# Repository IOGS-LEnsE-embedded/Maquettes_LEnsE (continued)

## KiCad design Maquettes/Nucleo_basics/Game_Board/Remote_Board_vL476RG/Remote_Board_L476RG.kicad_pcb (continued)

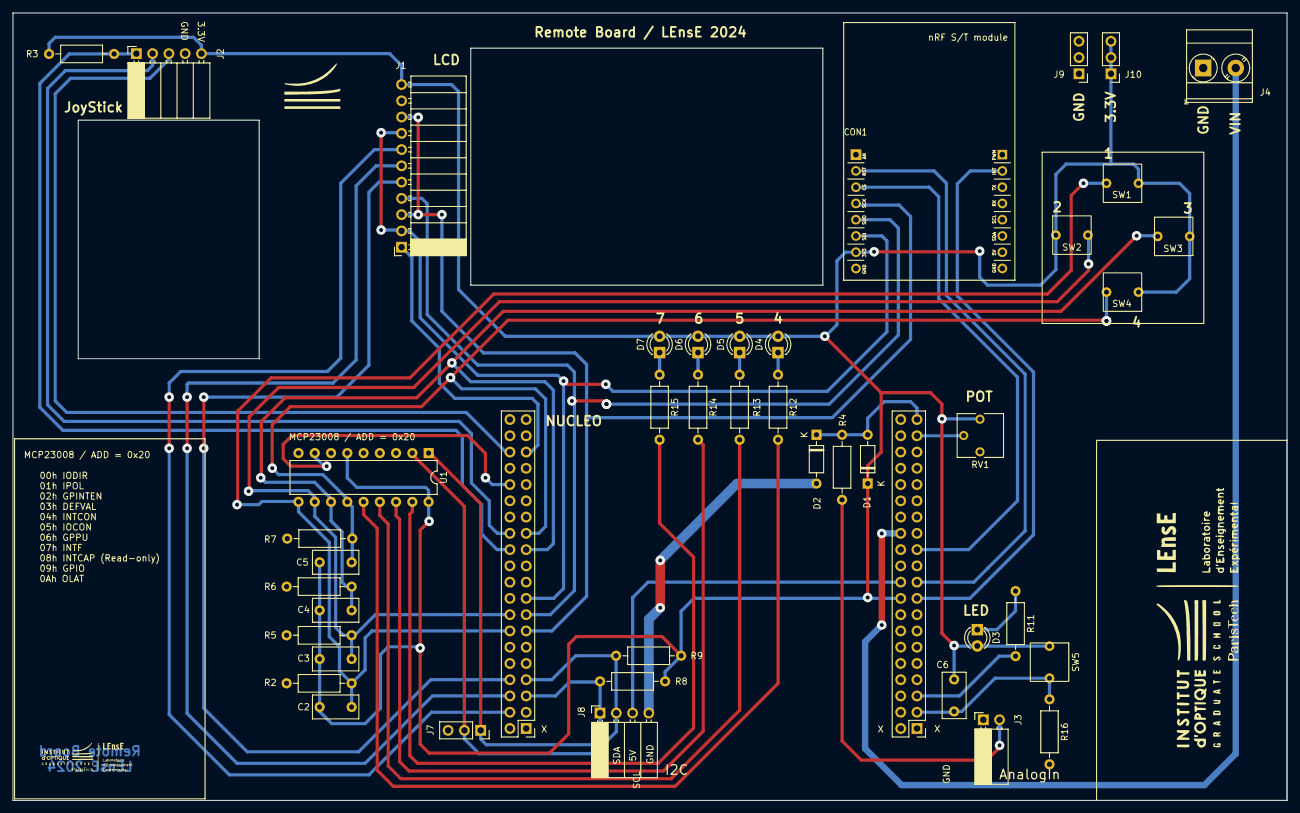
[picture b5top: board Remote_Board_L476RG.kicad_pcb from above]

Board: 2 copper layers, 199.0 x 123.0 mm, 44 parts (0 on the bottom side), 38 nets.

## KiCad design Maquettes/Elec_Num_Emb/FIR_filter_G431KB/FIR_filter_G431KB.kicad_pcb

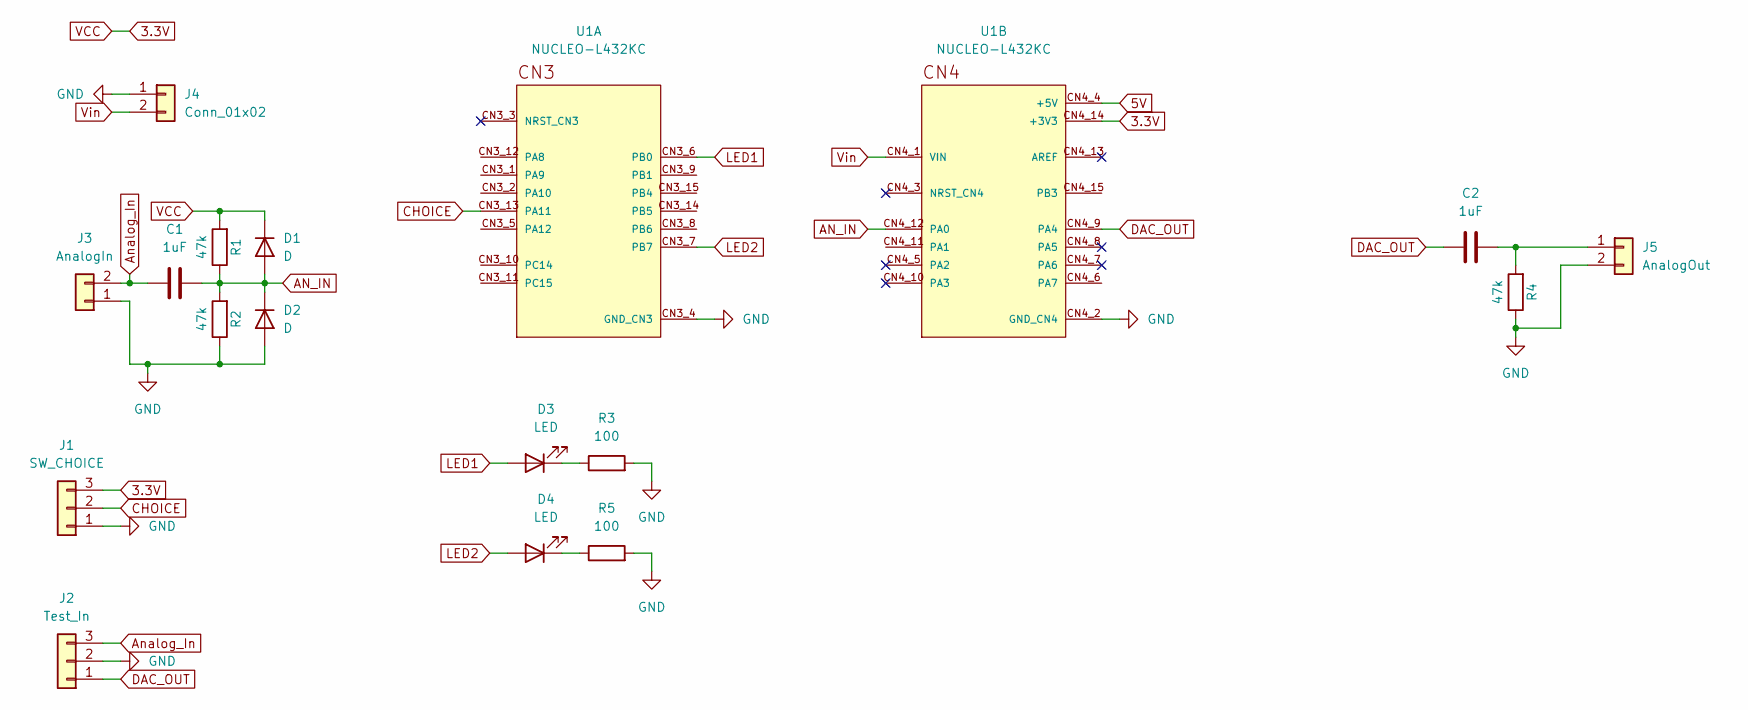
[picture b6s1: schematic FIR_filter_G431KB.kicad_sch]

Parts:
C1, C2: 1uF; C_Rect_L16.5mm_W7.3mm_P15.00mm_MKT
D1, D2: D; D_DO-35_SOD27_P7.62mm_Horizontal
D3, D4: LED; LED_D3.0mm_Clear
J1: SW_CHOICE; PinSocket_1x03_P2.54mm_Vertical
J2: Test_In; PinSocket_1x03_P2.54mm_Vertical
J3: AnalogIn; PinSocket_1x02_P2.54mm_Vertical
J4: Conn_01x02; PinSocket_1x02_P2.54mm_Vertical
J5: AnalogOut; PinSocket_1x02_P2.54mm_Vertical
R1, R2, R4: 47k; R_Axial_DIN0207_L6.3mm_D2.5mm_P10.16mm_Horizontal
R3, R5: 100; R_Axial_DIN0207_L6.3mm_D2.5mm_P10.16mm_Horizontal
U1: NUCLEO-L432KC; MODULE_NUCLEO-L432KC; PARTREV N/A

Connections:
3.3V: D1.1 (K), J1.3, R1.2, U1.CN4_14 (+3V3)
5V: U1.CN4_4 (+5V)
AN_IN: C1.2, D1.2 (A), D2.1 (K), R1.1, R2.2, U1.CN4_12 (PA0)
Analog_In: C1.1, J2.3, J3.2
CHOICE: J1.2, U1.CN3_13 (PA11)
DAC_OUT: C2.1, J2.1, U1.CN4_9 (PA4)
GND: D2.2 (A), J1.1, J2.2, J3.1, J4.1, J5.2, R2.1, R3.2, R4.1, R5.2, U1.CN3_4 (GND_CN3), U1.CN4_2 (GND_CN4)
LED1: D3.2 (A), U1.CN3_6 (PB0)
LED2: D4.2 (A), U1.CN3_7 (PB7)
unnamed: D3.1 (K), R3.1
unnamed: D4.1 (K), R5.1
unnamed: C2.2, J5.1, R4.2
Vin: J4.2, U1.CN4_1 (VIN)

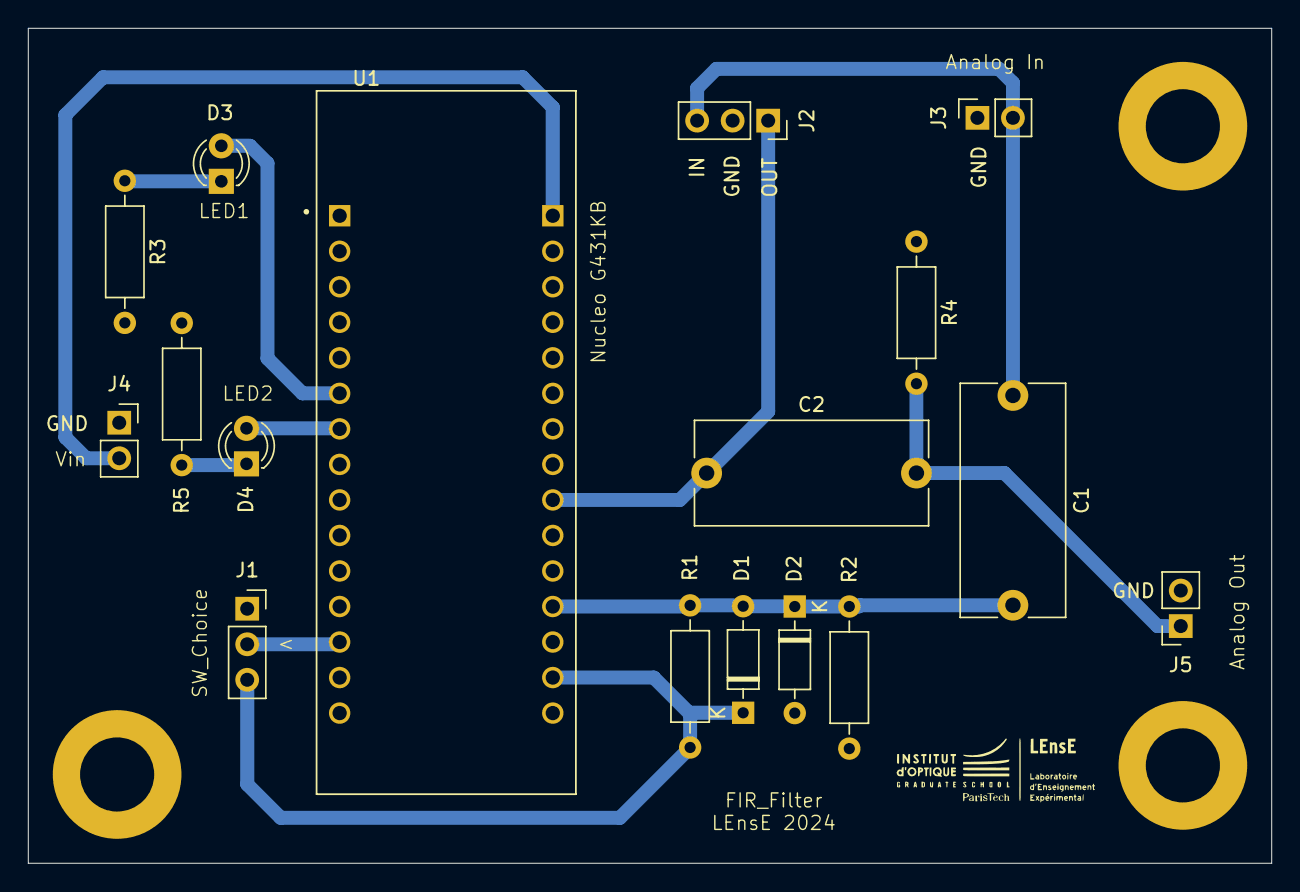
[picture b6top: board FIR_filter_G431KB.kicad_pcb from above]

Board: 2 copper layers, 88.9 x 59.7 mm, 17 parts (0 on the bottom side), 12 nets.

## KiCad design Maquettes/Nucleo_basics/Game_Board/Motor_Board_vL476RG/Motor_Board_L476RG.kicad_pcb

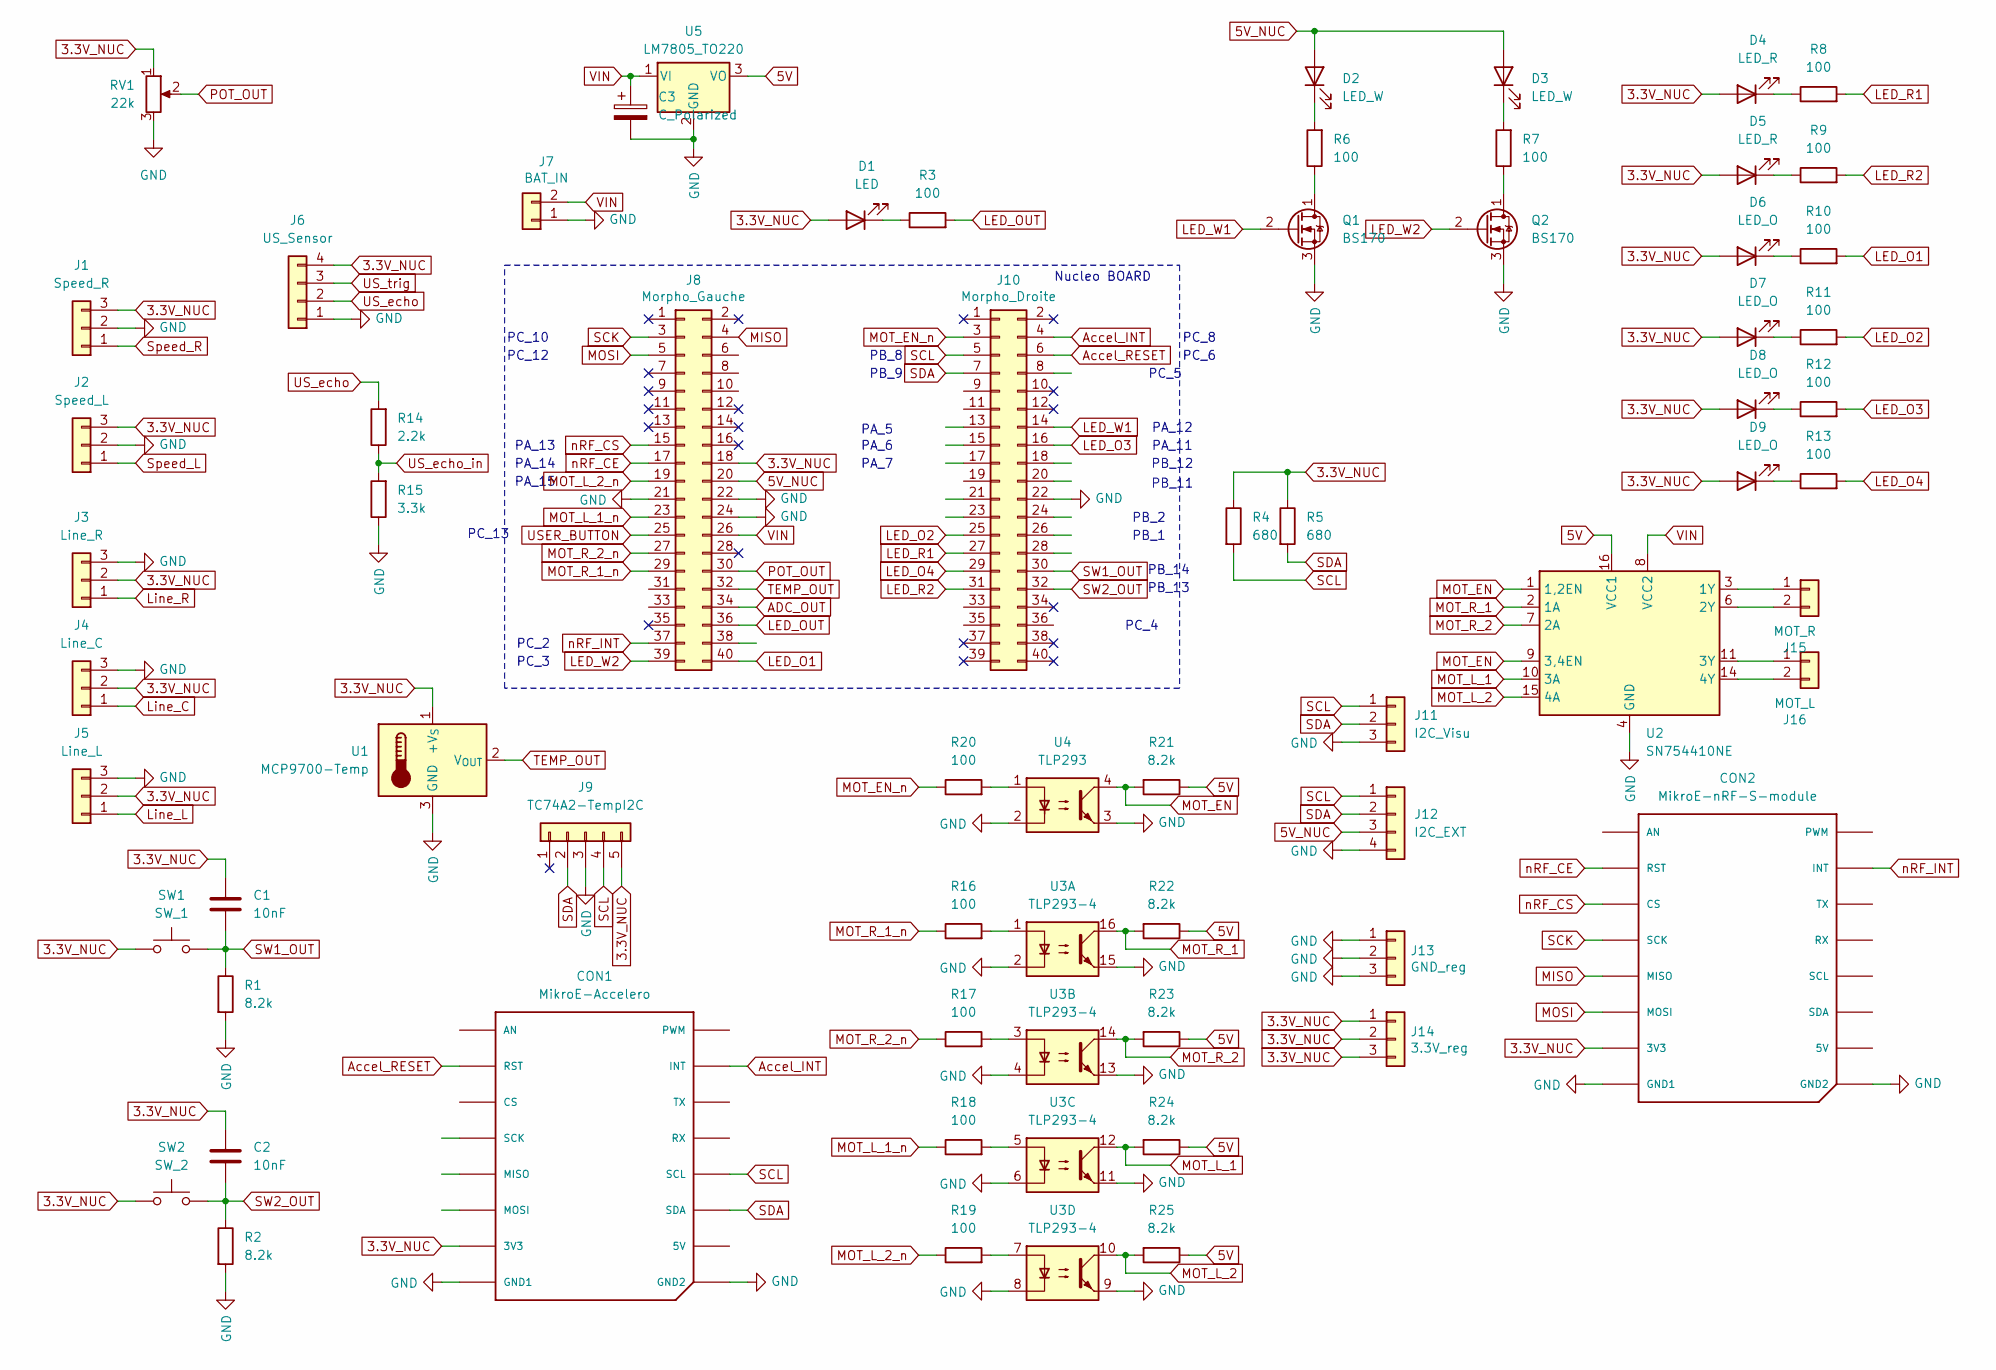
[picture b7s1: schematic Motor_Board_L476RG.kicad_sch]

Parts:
C1, C2: 10nF; C_Rect_L7.0mm_W3.5mm_P5.00mm
C3: C_Polarized; CP_Radial_D6.3mm_P2.50mm
CON1: MikroE-Accelero; MIKROBUS_MODULE_CONN
CON2: MikroE-nRF-S-module; MIKROBUS_MODULE_CONN
D1: LED; LED_D3.0mm_Clear
D2, D3: LED_W; LED_D3.0mm_Clear
D4, D5: LED_R; LED_D3.0mm_Clear
D6, D7, D8, D9: LED_O; LED_D3.0mm_Clear
J1: Speed_R; PinSocket_1x03_P2.54mm_Horizontal
J2: Speed_L; PinSocket_1x03_P2.54mm_Horizontal
J3: Line_R; PinSocket_1x03_P2.54mm_Horizontal
J4: Line_C; PinSocket_1x03_P2.54mm_Horizontal
J5: Line_L; PinSocket_1x03_P2.54mm_Horizontal
J6: US_Sensor; PinSocket_1x04_P2.54mm_Vertical
J7: BAT_IN; TerminalBlock_Phoenix_MKDS-3-2-5.08_1x02_P5.08mm_Horizontal
J8: Morpho_Gauche; PinHeader_2x20_P2.54mm_Vertical
J9: TC74A2-TempI2C; TO-220-5_Vertical
J10: Morpho_Droite; PinHeader_2x20_P2.54mm_Vertical
J11: I2C_Visu; PinSocket_1x03_P2.54mm_Vertical
J12: I2C_EXT; PinSocket_1x04_P2.54mm_Vertical
J13: GND_reg; PinHeader_1x03_P2.54mm_Vertical
J14: 3.3V_reg; PinHeader_1x03_P2.54mm_Vertical
J15: MOT_R; TerminalBlock_Phoenix_MKDS-3-2-5.08_1x02_P5.08mm_Horizontal
J16: MOT_L; TerminalBlock_Phoenix_MKDS-3-2-5.08_1x02_P5.08mm_Horizontal
Q1, Q2: BS170; TO-92_Inline
R1, R2, R21, R22, R23, R24, R25: 8.2k; R_Axial_DIN0207_L6.3mm_D2.5mm_P10.16mm_Horizontal
R3, R6, R7, R8, R9, R10, R11, R12, R13, R16, R17, R18, R19, R20: 100; R_Axial_DIN0207_L6.3mm_D2.5mm_P10.16mm_Horizontal
R4, R5: 680; R_Axial_DIN0207_L6.3mm_D2.5mm_P10.16mm_Horizontal
R14: 2.2k; R_Axial_DIN0207_L6.3mm_D2.5mm_P10.16mm_Horizontal
R15: 3.3k; R_Axial_DIN0207_L6.3mm_D2.5mm_P10.16mm_Horizontal
RV1: 22k; Potentiometer_Bourns_3386P_Vertical
SW1: SW_1; Switch
SW2: SW_2; Switch
U1: MCP9700-Temp; TO-92_Inline
U2: SN754410NE; DIP-16_W7.62mm
U3: TLP293-4; SOIC-16_4.55x10.3mm_P1.27mm
U4: TLP293; SOIC-4_4.55x2.6mm_P1.27mm
U5: LM7805_TO220; TO-220-3_Vertical

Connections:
3.3V_NUC: C1.1, C2.1, CON1.P7 (3V3), CON2.P7 (3V3), D1.2 (A), D4.2 (A), D5.2 (A), D6.2 (A), D7.2 (A), D8.2 (A), D9.2 (A), J1.3, J2.3, J3.2, J4.2, J5.2, J6.4, J8.18, J9.5, J14.1, J14.2, J14.3, R4.1, R5.1, RV1.1, SW1.1, SW2.1, U1.1 (+V_{S})
5V: R21.1, R22.1, R23.1, R24.1, R25.1, U2.16 (VCC1), U5.3 (VO)
5V_NUC: D2.2 (A), D3.2 (A), J8.20, J12.3
ADC_OUT: J8.34
Accel_INT: CON1.P15 (INT), J10.4
Accel_RESET: CON1.P2 (RST), J10.6
GND: C3.2, CON1.P8 (GND1), CON1.P9 (GND2), CON2.P8 (GND1), CON2.P9 (GND2), J1.2, J2.2, J3.3, J4.3, J5.3, J6.1, J7.1, J8.21, J8.22, J8.24, J9.3, J10.22, J11.3, J12.4, J13.1, J13.2, J13.3, Q1.3 (S), Q2.3 (S), R1.2, R2.2, R15.1, RV1.3, U1.3 (GND), U2.4 (GND), U2.5 (GND), U2.12 (GND), U2.13 (GND), U3.2, U3.4, U3.6, U3.8, U3.9, U3.11, U3.13, U3.15, U4.2, U4.3, U5.2 (GND)
LED_O1: J8.40, R10.2
LED_O2: J10.25, R11.2
LED_O3: J10.16, R12.2
LED_O4: J10.29, R13.2
LED_OUT: J8.36, R3.2
LED_R1: J10.27, R8.2
LED_R2: J10.31, R9.2
LED_W1: J10.14, Q1.2 (G)
LED_W2: J8.39, Q2.2 (G)
Line_C: J4.1
Line_L: J5.1
Line_R: J3.1
MISO: CON2.P5 (MISO), J8.4
MOSI: CON2.P6 (MOSI), J8.5
MOT_EN: R21.2, U2.1 (1,2EN), U2.9 (3,4EN), U4.4
MOT_EN_n: J10.3, R20.1
MOT_L_1: R24.2, U2.10 (3A), U3.12
MOT_L_1_n: J8.23, R18.1
MOT_L_2: R25.2, U2.15 (4A), U3.10
MOT_L_2_n: J8.19, R19.1
MOT_R_1: R22.2, U2.2 (1A), U3.16
MOT_R_1_n: J8.29, R16.1
MOT_R_2: R23.2, U2.7 (2A), U3.14
MOT_R_2_n: J8.27, R17.1
unnamed: D1.1 (K), R3.1
unnamed: D2.1 (K), R6.2
unnamed: D3.1 (K), R7.2
unnamed: D4.1 (K), R8.1
unnamed: D5.1 (K), R9.1
unnamed: D6.1 (K), R10.1
unnamed: D7.1 (K), R11.1
unnamed: D8.1 (K), R12.1
unnamed: D9.1 (K), R13.1
unnamed: J15.1, U2.3 (1Y)
unnamed: J15.2, U2.6 (2Y)
unnamed: J16.1, U2.11 (3Y)
unnamed: J16.2, U2.14 (4Y)
unnamed: Q1.1 (D), R6.1
unnamed: Q2.1 (D), R7.1
unnamed: R16.2, U3.1
unnamed: R17.2, U3.3
unnamed: R18.2, U3.5
unnamed: R19.2, U3.7
unnamed: R20.2, U4.1
POT_OUT: J8.30, RV1.2
SCK: CON2.P4 (SCK), J8.3
SCL: CON1.P12 (SCL), J9.4, J10.5, J11.1, J12.1, R4.2
SDA: CON1.P11 (SDA), J9.2, J10.7, J11.2, J12.2, R5.2
SW1_OUT: C1.2, J10.30, R1.1, SW1.2
SW2_OUT: C2.2, J10.32, R2.1, SW2.2
Speed_L: J2.1
Speed_R: J1.1
TEMP_OUT: J8.32, U1.2 (V_{OUT})
USER_BUTTON: J8.25
US_echo: J6.2, R14.2
US_echo_in: R14.1, R15.2
US_trig: J6.3
VIN: C3.1, J7.2, J8.26, U2.8 (VCC2), U5.1 (VI)
nRF_CE: CON2.P2 (RST), J8.17
nRF_CS: CON2.P3 (CS), J8.15
nRF_INT: CON2.P15 (INT), J8.37

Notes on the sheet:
PA_12
PC_2
PB_8
PA_7
PC_8
PA_5
PB_13
PA_14
PB_11
PB_9
PC_5
PB_2
PC_12
PB_14
PC_13
PA_15
PC_10
PA_11
PC_4
PA_6
PA_13
Nucleo BOARD
PB_12
PC_3
PB_1
PC_6

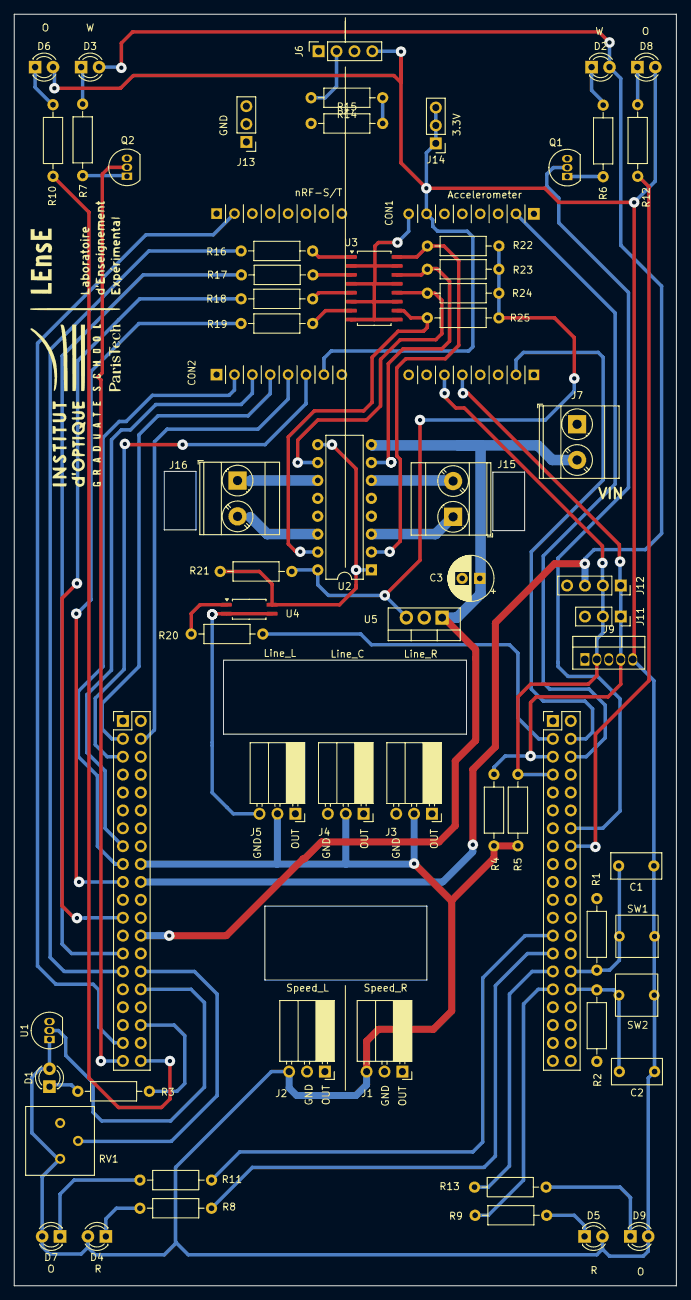
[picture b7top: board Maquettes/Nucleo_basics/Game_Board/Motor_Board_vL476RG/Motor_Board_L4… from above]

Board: 2 copper layers, 94.0 x 180.5 mm, 65 parts (0 on the bottom side), 60 nets.

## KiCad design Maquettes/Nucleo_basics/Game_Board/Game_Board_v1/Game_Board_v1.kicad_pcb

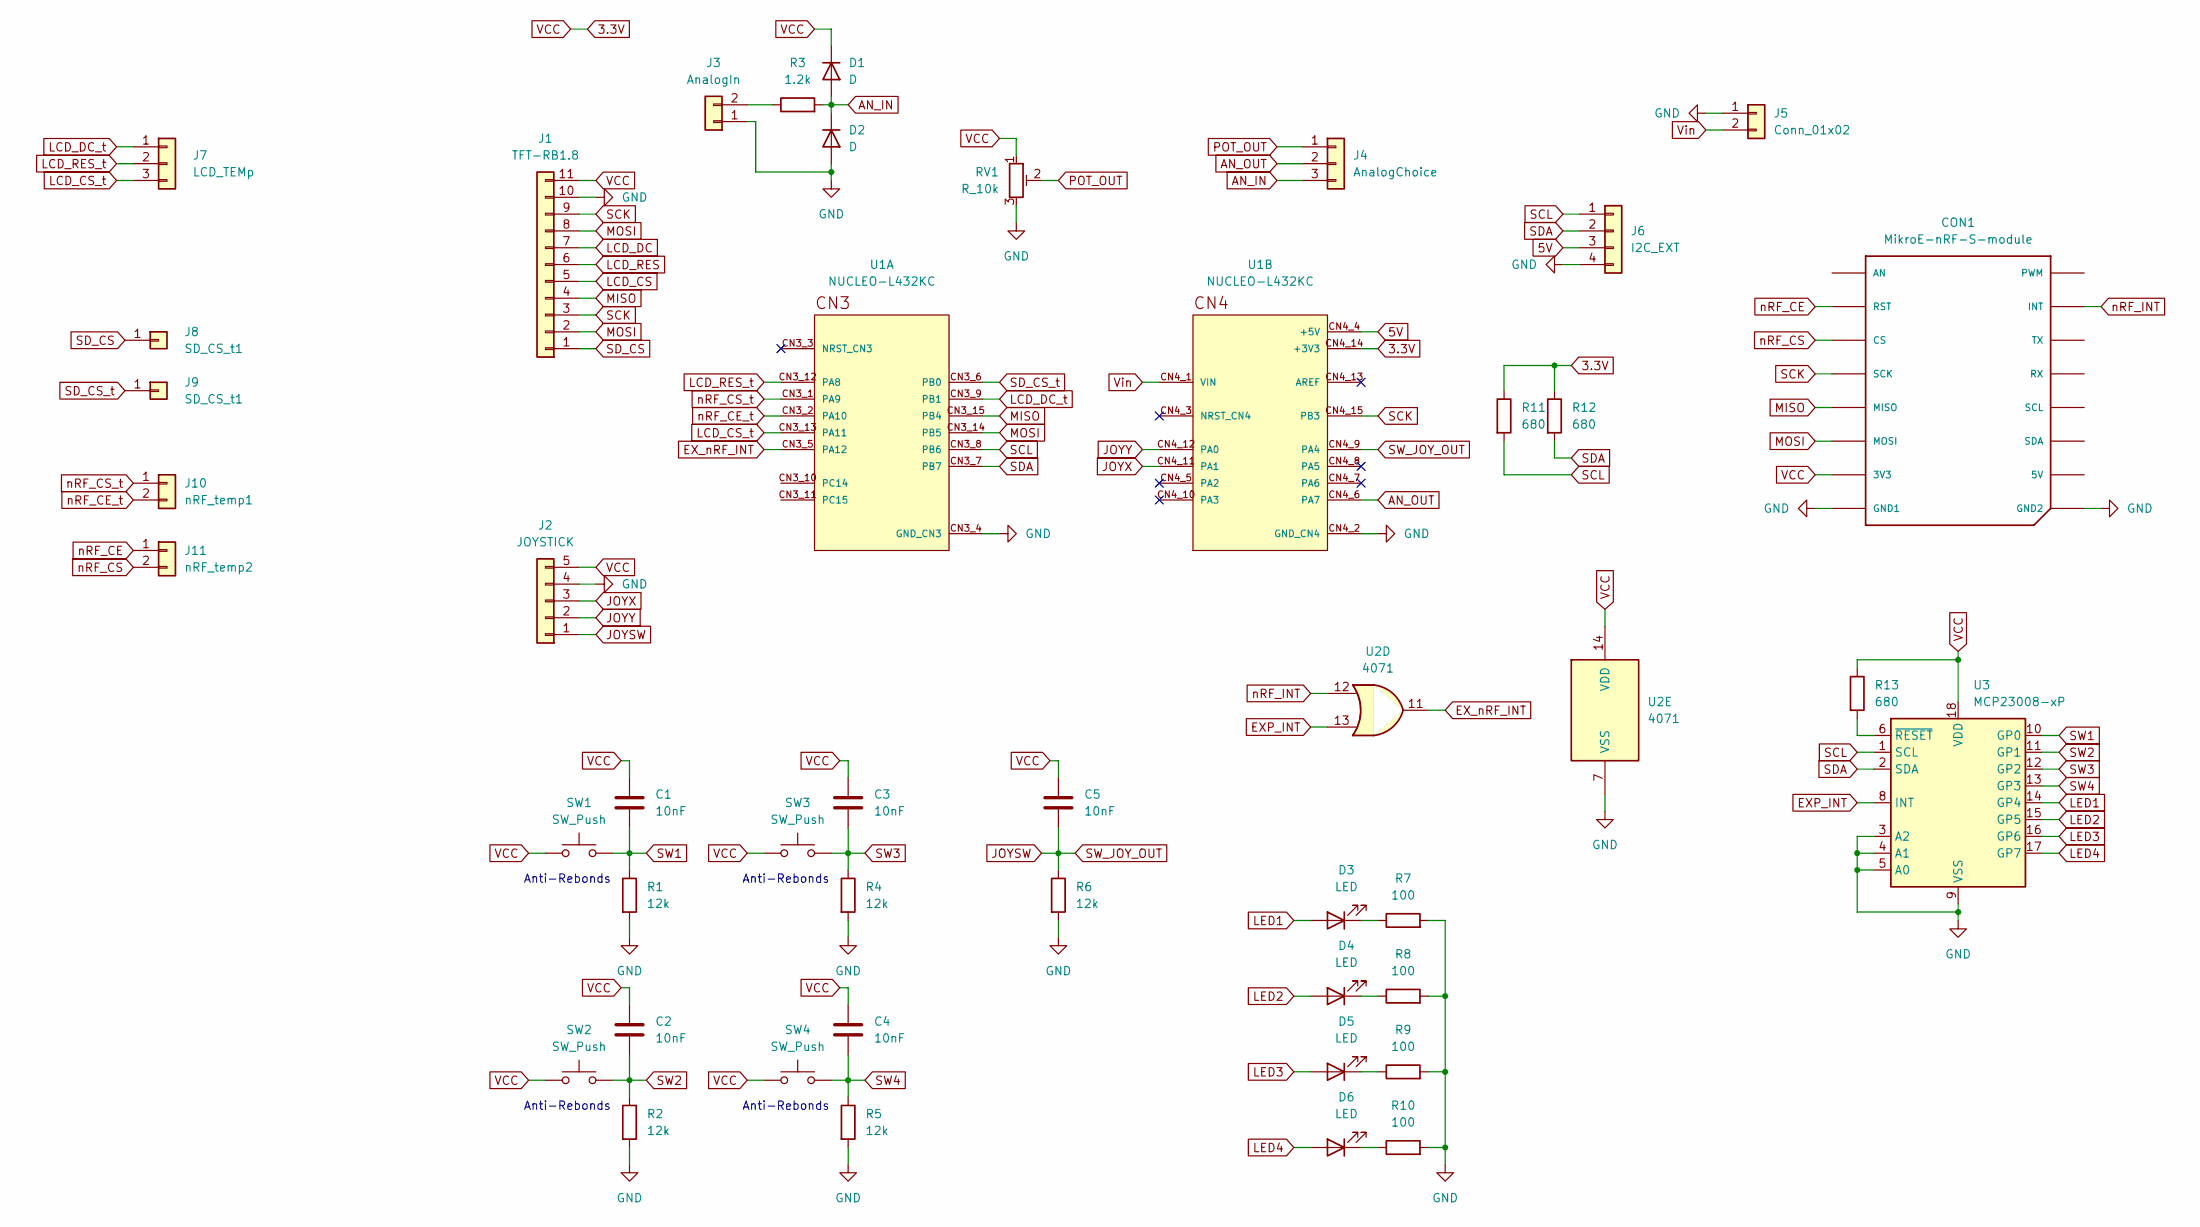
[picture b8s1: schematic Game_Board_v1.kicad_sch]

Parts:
C1, C2, C3, C4, C5: 10nF; C_Rect_L7.0mm_W3.5mm_P5.00mm
CON1: MikroE-nRF-S-module; MIKROBUS_HOST_CONN
D1, D2: D; D_DO-35_SOD27_P7.62mm_Horizontal
D3, D4, D5, D6: LED; LED_D3.0mm_Clear
J1: TFT-RB1.8; PinSocket_1x11_P2.54mm_Horizontal
J2: JOYSTICK; PinSocket_1x05_P2.54mm_Horizontal
J3: AnalogIn; PinSocket_1x02_P2.54mm_Horizontal
J4: AnalogChoice; PinHeader_1x03_P2.54mm_Horizontal
J5: Conn_01x02; TerminalBlock_Phoenix_PT-1,5-2-5.0-H_1x02_P5.00mm_Horizontal
J6: I2C_EXT; PinHeader_1x04_P2.54mm_Horizontal
J7: LCD_TEMp; PinSocket_1x03_P2.54mm_Vertical
J8, J9: SD_CS_t1; PinSocket_1x01_P2.54mm_Vertical
J10: nRF_temp1; PinSocket_1x02_P2.54mm_Vertical
J11: nRF_temp2; PinSocket_1x02_P2.54mm_Vertical
R1, R2, R4, R5, R6: 12k; R_Axial_DIN0207_L6.3mm_D2.5mm_P10.16mm_Horizontal
R3: 1.2k; R_Axial_DIN0207_L6.3mm_D2.5mm_P10.16mm_Horizontal
R7, R8, R9, R10: 100; R_Axial_DIN0207_L6.3mm_D2.5mm_P10.16mm_Horizontal
R11, R12, R13: 680; R_Axial_DIN0207_L6.3mm_D2.5mm_P10.16mm_Horizontal
RV1: R_10k; Potentiometer_Vishay_T73YP_Vertical
SW1, SW2, SW3, SW4: SW_Push; Switch
U1: NUCLEO-L432KC; MODULE_NUCLEO-L432KC; PARTREV N/A
U2: 4071; DIP-14_W7.62mm_Socket_LongPads
U3: MCP23008-xP; DIP-18_W7.62mm

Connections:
3.3V: C1.1, C2.1, C3.1, C4.1, C5.1, CON1.P7 (3V3), D1.1 (K), J1.11, J2.5, R11.1, R12.1, R13.1, RV1.1, SW1.1, SW2.1, SW3.1, SW4.1, U1.CN4_14 (+3V3), U2.14 (VDD), U3.18 (VDD)
5V: J6.3, U1.CN4_4 (+5V)
AN_IN: D1.2 (A), D2.1 (K), J4.3, R3.2
AN_OUT: J4.2, U1.CN4_6 (PA7)
EXP_INT: U2.13, U3.8 (INT)
EX_nRF_INT: U1.CN3_5 (PA12), U2.11
GND: CON1.P8 (GND1), CON1.P9 (GND2), D2.2 (A), J1.10, J2.4, J3.1, J5.1, J6.4, R1.2, R2.2, R4.2, R5.2, R6.2, R7.2, R8.2, R9.2, R10.2, RV1.3, U1.CN3_4 (GND_CN3), U1.CN4_2 (GND_CN4), U2.7 (VSS), U3.3 (A2), U3.4 (A1), U3.5 (A0), U3.9 (VSS)
JOYSW: C5.2, J2.1, R6.1, U1.CN4_9 (PA4)
JOYX: J2.3, U1.CN4_11 (PA1)
JOYY: J2.2, U1.CN4_12 (PA0)
LCD_CS: J1.5
LCD_CS_t: J7.3, U1.CN3_13 (PA11)
LCD_DC: J1.7
LCD_DC_t: J7.1, U1.CN3_9 (PB1)
LCD_RES: J1.6
LCD_RES_t: J7.2, U1.CN3_12 (PA8)
LED1: D3.2 (A), U3.14 (GP4)
LED2: D4.2 (A), U3.15 (GP5)
LED3: D5.2 (A), U3.16 (GP6)
LED4: D6.2 (A), U3.17 (GP7)
MISO: CON1.P5 (MISO), J1.4, U1.CN3_15 (PB4)
MOSI: CON1.P6 (MOSI), J1.2, J1.8, U1.CN3_14 (PB5)
unnamed: D3.1 (K), R7.1
unnamed: D4.1 (K), R8.1
unnamed: D5.1 (K), R9.1
unnamed: D6.1 (K), R10.1
unnamed: J3.2, R3.1
unnamed: R13.2, U3.6 (~RESET)
POT_OUT: J4.1, RV1.2
SCK: CON1.P4 (SCK), J1.3, J1.9, U1.CN4_15 (PB3)
SCL: J6.1, R11.2, U1.CN3_8 (PB6), U3.1 (SCL)
SDA: J6.2, R12.2, U1.CN3_7 (PB7), U3.2 (SDA)
SD_CS: J1.1, J8.1
SD_CS_t: J9.1, U1.CN3_6 (PB0)
SW1: C1.2, R1.1, SW1.2, U3.10 (GP0)
SW2: C2.2, R2.1, SW2.2, U3.11 (GP1)
SW3: C3.2, R4.1, SW3.2, U3.12 (GP2)
SW4: C4.2, R5.1, SW4.2, U3.13 (GP3)
Vin: J5.2, U1.CN4_1 (VIN)
nRF_CE: CON1.P2 (RST), J11.1
nRF_CE_t: J10.2, U1.CN3_2 (PA10)
nRF_CS: CON1.P3 (CS), J11.2
nRF_CS_t: J10.1, U1.CN3_1 (PA9)
nRF_INT: CON1.P15 (INT), U2.12

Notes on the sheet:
Anti-Rebonds

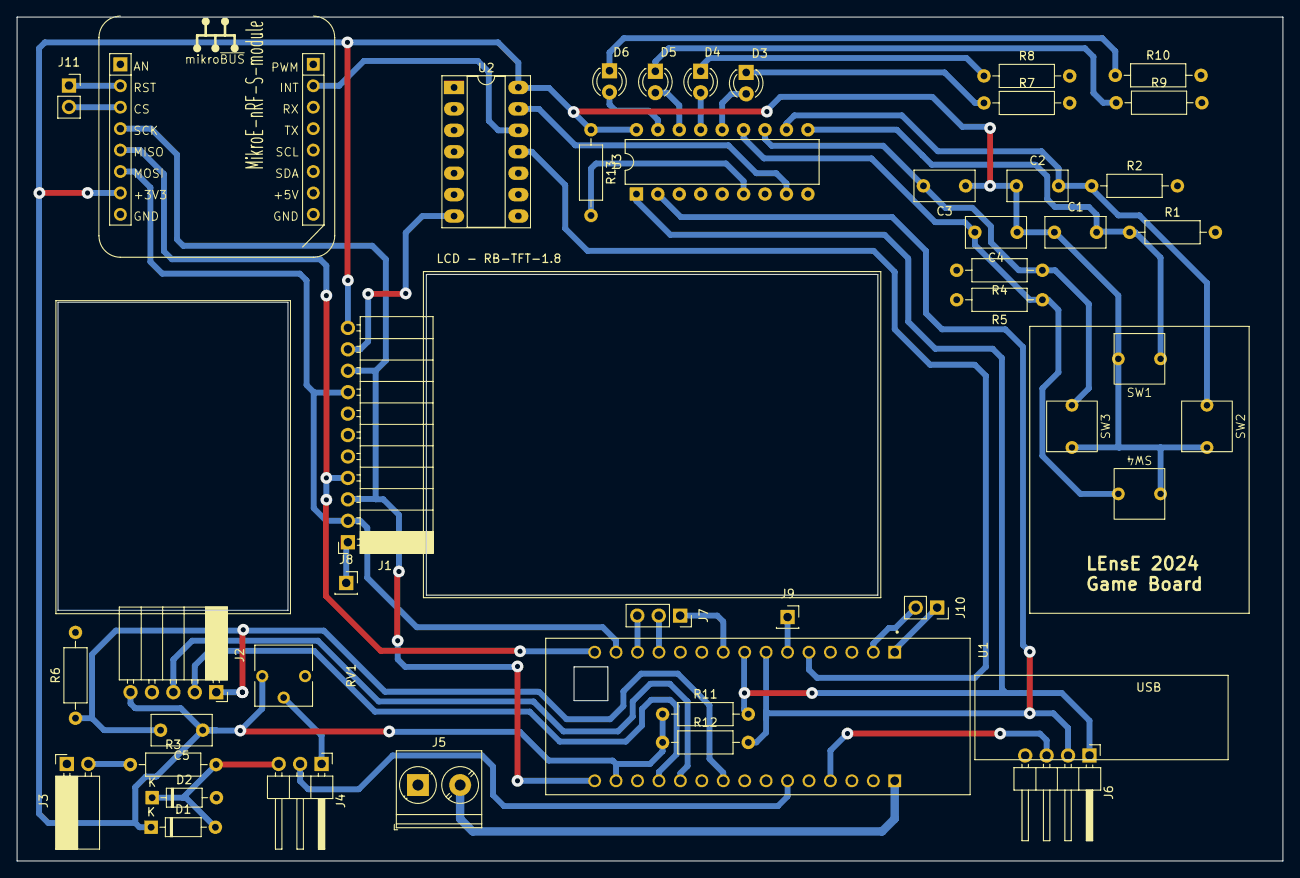
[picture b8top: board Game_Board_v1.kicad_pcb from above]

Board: 2 copper layers, 150.0 x 100.0 mm, 44 parts (0 on the bottom side), 41 nets.

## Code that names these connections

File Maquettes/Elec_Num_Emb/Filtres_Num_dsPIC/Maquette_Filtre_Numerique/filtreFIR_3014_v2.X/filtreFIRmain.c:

/*
--------------------------------------------------------------------------------
-- LEnsE - Institut Optique Graduate School
-- 	Julien VILLEMEJANE
--		2019-05-08
--
--		LEnsE Project - Filtre numerique
--		dsPIC30F4013 - FIR Filter
--------------------------------------------------------------------------------
 * RF0  -> Test Output
 * RD3  -> Choix Mode / Input
 * RB9  -> Analog In / Input
 * RF2/RF3/RF6 -> SDI/SDO/SCK - SPI Input,Output,Output
 * RD8/RD2 -> DAC_CS/DAC_LD - Output    - DAC type MCP4921 / 12 bits
 * RB11  -> ADC_CS - Output             - ADC type MCP3201 / 12 bits
 * RB10/RB0/RB1  -> Not Used PCB Input
 */

#include <xc.h>
#include "config.h"     // PLLx8 -> FOSC = 58,96 MHz
#include "FIR_Filter.h"
#include "FIR_band_2.3k_3.7k_40dB_Fs20k.h"

#define     TEST_OUT    LATFbits.LATF0
#define     DAC_CS      LATDbits.LATD8
#define     DAC_LD      LATDbits.LATD2
#define     ADC_CS      LATBbits.LATB11
#define     CHOIX_MODE  PORTDbits.RD3

// Global variables definition
int measure;
int i;
int output;

// SPI INIT
void initSPI(void)
{
    SPI1STAT = 0x0000;
    SPI1CON = 0x0020;      //Set the SPI1 module to 8-bit Master mode
    SPI1CONbits.SPRE = 0b101;   // Prediv = 1:1
    SPI1CONbits.PPRE = 0b10;    // Postdiv = 1:4
    IFS0bits.SPI1IF = 0;    //Clear the SPI1 Interrupt Flag
    IEC0bits.SPI1IE = 0;    //SPI1 ISR processing is not enabled.
                            //SPI1 will be used in polling-mode
    SPI1STATbits.SPIEN = 1; //Turn on the SPI1 module
}

// ADC 
int convertADC(void){
    int value = 0;
    char temp, data1, data2;
    ADC_CS = 0;
    temp = SPI1BUF;
    SPI1STATbits.SPIROV = 0;
    IFS0bits.SPI1IF = 0;
    SPI1BUF = 0;
    while (IFS0bits.SPI1IF==0);
    ADC_CS = 0;
    ADC_CS = 0;  
    data1 = SPI1BUF;
    SPI1STATbits.SPIROV = 0;
    IFS0bits.SPI1IF = 0;
    SPI1BUF = 0;
    while (IFS0bits.SPI1IF==0);
    ADC_CS = 0;
    ADC_CS = 0;  
    data2 = SPI1BUF;
    ADC_CS = 1;
    value = (data1 & 0b00111111) << 6;
    value += (data2 & 0b11111100) >> 2;
    return value;
}

// DAC writing subroutine
void sendToDAC(int value){
    char temp, data1, data2;
    data1 = ((value & 0x0F00) >> 8) + 0b00110000; 
    data2 = (value & 0xFF);
    DAC_CS = 0;
    DAC_CS = 0;
    temp = SPI1BUF;
    SPI1STATbits.SPIROV = 0;
    IFS0bits.SPI1IF = 0;
    SPI1BUF = data1;
    while (IFS0bits.SPI1IF==0);
    DAC_CS = 0;
    temp = SPI1BUF;
    SPI1STATbits.SPIROV = 0;
    IFS0bits.SPI1IF = 0;
    SPI1BUF = data2;
    while (IFS0bits.SPI1IF==0);
    DAC_CS = 1;
    DAC_LD = 0;
    DAC_LD = 0;
    DAC_LD = 1;
    return;
}

// TIMER
void initTMR1(void){
    IPC0bits.T1IP = 7;  // interrupt priority
    IEC0bits.T1IE = 0;  // interruption timer
    IFS0bits.T1IF = 0;  // flag d'interruption remis à zéro
    T1CONbits.TCKPS = 0;    // 0 - PDIV = 1 / 1 - PDIV = 8 / 2 - PDIV = 64 / 3 - PDIV = 256
    T1CONbits.TCS = 0;  // internal source
    T1CONbits.TSIDL = 0;
    T1CONbits.TGATE = 0;
    PR1 = 1533;    // 16 bits !
    PR1 = 1480;
    // FTMR1 = FCYC / PREDIV / (PR1 + 1) = 30.68 MHz / 1 / 1
    T1CONbits.TON = 1; // démarrage du timer
    IEC0bits.T1IE = 1;
}

void __attribute__((__interrupt__, __auto_psv__)) _T1Interrupt (void)
{
    TEST_OUT = !TEST_OUT;
    measure = convertADC();
    //TMR1 = 0; // remise à 0 du compteur
    if(CHOIX_MODE == 1){   // Mode filtre
        measure -= 2048;
        BlockFIRFilter( &FIR_band_2Filter, &measure, &output, 1);
        output = output << 1;
        output += 2048;
    }
    else{   // Mode suiveur
        output = measure;
        output = output << 1;
    }
    sendToDAC(output);
    IFS0bits.T1IF=0; // remise à 0 du drapeau d?interruption du timer
}

// Initialization subroutine
void initPIC(){
    // Oscillator
    OSCCONbits.COSC = 0b001;    // FRC - Nominal - 7.67 MHz
    OSCCONbits.NOSC = 0b001;    // FRC
    // Avec PLL 16x / config.h 
    //      -->  FOSC = 16 x 7.67 MHz = 122.72 MHz
    //      -->  FCYC = FOSC / 4 = 30.68 MHz --> TCYC = 32.6 ns
    OSCTUN = 0;
    
    // Input/Output
    TRISFbits.TRISF0 = 0;   // RD0 - Test Output
    TRISDbits.TRISD3 = 1;   // RD3 - Mode choice Input
    
    TRISFbits.TRISF2 = 1;   // RF2 - SDI SPI Input
    TRISFbits.TRISF3 = 0;   // RF3 - SDO SPI Output
    TRISFbits.TRISF6 = 0;   // RF6 - SCK SPI Output

    TRISDbits.TRISD8 = 0;   // RD8 - DAC_CS Output
    TRISDbits.TRISD2 = 0;   // RD2 - DAC_LD Output
    DAC_CS = 1;
    DAC_LD = 1;
    
    TRISBbits.TRISB11 = 0;  // RB11 - ADC_CS Output
    ADC_CS = 1;
    
    TRISBbits.TRISB10 = 1;  // RB10 - PCB Input
    TRISBbits.TRISB0 = 1;   // RB0 - PCB Input
    TRISBbits.TRISB1 = 1;   // RB1 - PCB Input
    
    // Analog Input
    ADPCFG=0xFFFF;          // All pins in digital mode
    ADPCFGbits.PCFG9 = 0;   // AN9 in analog mode / Analog In
    ADCSSL = 0;             // No analog inputs in the scanning list
    ADCSSLbits.CSSL9 = 1;   // AN9 in scanning list
    // Filter initialiation
	FIRFilterInit( &FIR_band_2Filter);
    // Interrupts configuration
	INTCON1bits.NSTDIS = 0 ;    // Interrupt nesting is enabled
    IEC0bits.T1IE = 1;          // Interrupt on TMR1
    // Variables initialization
	measure = 0;
	output = 0;
}

// Main program
int main(void) {        
    initPIC();
    initSPI();
    initTMR1();
    while(1);
}

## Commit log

2023-04-18 Transfer from jvillemejane
2023-04-18 Updating Brochage/Procedure Robot Holonome
2023-04-24 Update Notice Robot Holonome
2023-11-20 Adding AetS Spectrum Project
2023-11-21 Update AetS Spectrum
2023-11-25 Update Maquettes
2023-11-29 Update Spectrum AetS
2023-12-05 Update Arts Et Sciences
2023-12-05 Update Arts Et Sciences Spectrum
2023-12-05 Update ArtsEtSciences Spectrum
2023-12-21 Adding docs
2023-12-21 Update Sphinx Doc and GitHub Pages update
2023-12-21 deploy: e28df9af5b651e778c9244612c0f5e063d7eaf0c
2023-12-22 Update Documentation
2023-12-22 deploy: dd3a48548c9755995df42aa203ef30fe2f5c733e
2023-12-22 Update documentation of Machine Vision
2023-12-22 deploy: e61b2c0f57005e0710918c51e2a0f09a5ebeec3c
2023-12-22 deploy: aa7ae83a8913076ebed6941b49867580efe00572
2023-12-22 Update documentation structure
2023-12-22 deploy: 3737ed34a4663262f0a38f1aa6b1158fe919967b
2024-01-07 deploy: 610032627cfd9d76ab5a4329a5263e82adedf73a
2024-01-13 deploy: 2b7037b7bece01c3d0a5f4185c5b28953b8d3ede
2024-01-13 deploy: 9c4e89d0e06544cac8d9fe29eb386aa0a233ce29
2024-01-16 Update DMX MBED6
2024-02-01 Update Maquette DMX
2024-02-16 Adding MCP library to translate (EA DOG LCD)
2024-02-16 Remove (and move) LCD to MBED Library
2024-03-08 Remove DMX
2024-03-11 Move RB-TFT18
2024-03-13 Adding Nucleo_basics_Game_Board
2024-03-14 GameBoard NucleoBasics update
2024-03-14 Update GameBoard
2024-03-15 Create DemoBoard PhD/LED
2024-03-15 Amplifier Demo Board
2024-03-27 Update GameBoard project
2024-03-27 Adding connectors for GameBoard v1
2024-04-09 Update Gameboard
    Change Joystick connector !!
2024-05-19 deploy: a258be7aba4208ebd17be04f1933119ac68a11ed
2024-05-19 Update Game Board
2024-05-21 Update Board for Nucleo Basics
2024-05-21 Update Board
2024-05-21 Update Remote L476RG
2024-05-22 Update Remote Board
2024-05-22 Update Remote Board / L476RG version
2024-05-22 Update Remote Board / L476RG
2024-05-26 Update Remote and Robot Nucleo basics
2024-05-26 Update Robot Board
    ATTENTION : Déplacer la carte Nucléo (ou changer sens mais bcp de modif...)
    Tester SPI avec MISO:PC_11, MISO:PC_12, SCK:PC_10
2024-05-27 Update Robot Board
2024-05-27 Update Remote and Robot boards / Nucleo Basics
2024-05-27 Update Nucleo Basics / Remote and Robot Boards
2024-05-28 Update Motor Board
2024-05-28 Update Remote and Robot Boards
2024-05-29 Update Boards
2024-05-29 Update Motor Board / Add FIR Filter
2024-05-29 Update Robot and Remote Boards
2024-06-10 Update Filtre FIR sur dsPIC
2024-06-10 Add Maquette Modulation AM
2024-07-17 deploy: 52e2781d987936dc39d795c82e5bdd5514504930
2024-08-23 Update Robot board for Joy It Car
2024-08-23 Test robot board with L476RG (to continue)
2024-08-23 Update PCB of robot board
2024-08-24 Update Test of joy-it car board robot
2024-08-27 Update Robot Test
2024-09-05 Update Test of Robot board
2024-09-27 Adding rayonnement
2024-10-04 Update Rayonnement Schematics
2024-10-05 Update Rayonnement
2024-10-06 Update Robot and Lighting Diagram boards
2024-10-06 Update Robot and light diagram boards
2024-10-06 Update Radiation DIagram Board
2024-10-08 deploy: e605fb3aeb05a111ce0af96c2ea1cfd61647b28a
2024-10-18 deploy: f120b89bce94992850497bd76e163ba7d64d4149
2024-10-18 Adding PCB/SCH pdf
2024-10-19 Update Schema of Robot board
2024-10-26 Update Robot Schematic
2024-10-27 remove old boards
2024-10-29 Update Radiation board schematic
2025-02-13 deploy: a246ee841c78e9729b533e806e65242825468efd
2025-03-28 Update FIR Filter on G431KB schematic (PDF only)
2025-03-28 deploy: e31cd89a59be33186b005ba34ba8d4f558ddbb56
2025-03-29 Update FIR Filter on G431KB / FIR code using CMSIS DSP in CubeIDE
